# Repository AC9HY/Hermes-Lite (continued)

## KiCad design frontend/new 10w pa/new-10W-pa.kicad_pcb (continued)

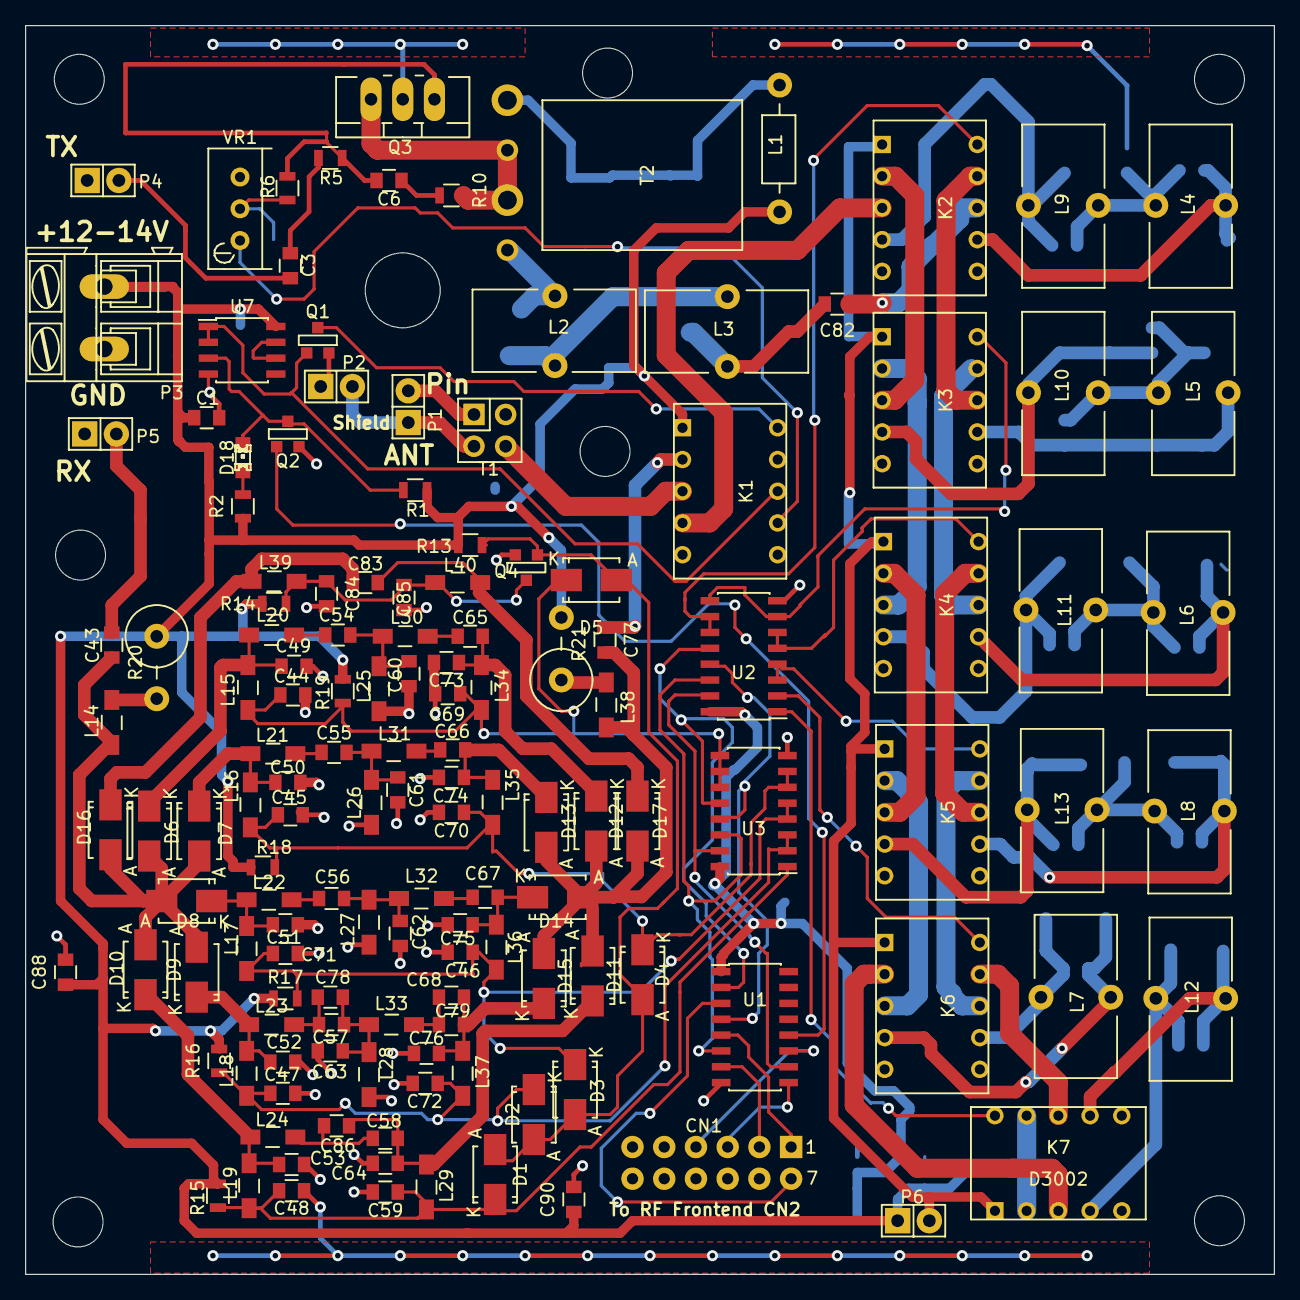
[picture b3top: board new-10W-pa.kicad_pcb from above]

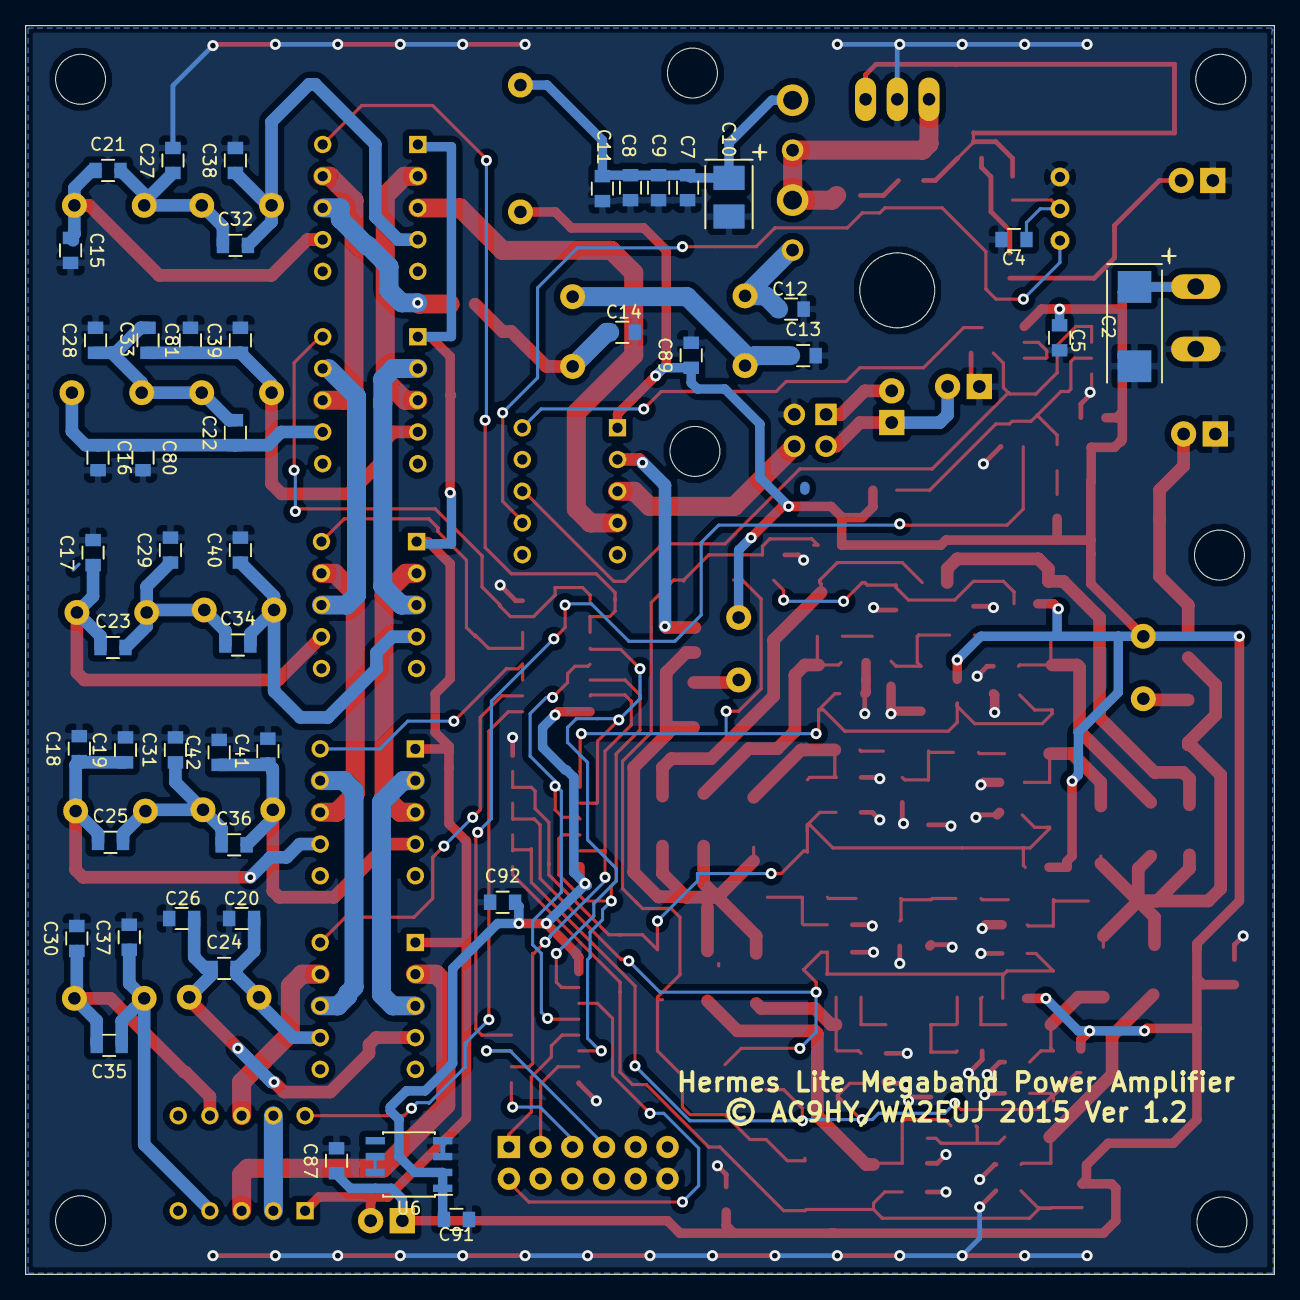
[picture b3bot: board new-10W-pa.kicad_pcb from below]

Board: 2 copper layers, 100.0 x 100.0 mm, 198 parts (46 on the bottom side), 107 nets.

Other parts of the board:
MountingHole_4mm, MountingHole_4mm#2, MountingHole_4mm#3, MountingHole_4mm#4, MountingHole_4mm#5, MountingHole_4mm#6, MountingHole_4mm#7: VAL**; MountingHole_4mm
MountingHole_6mm: VAL**; MountingHole_6mm

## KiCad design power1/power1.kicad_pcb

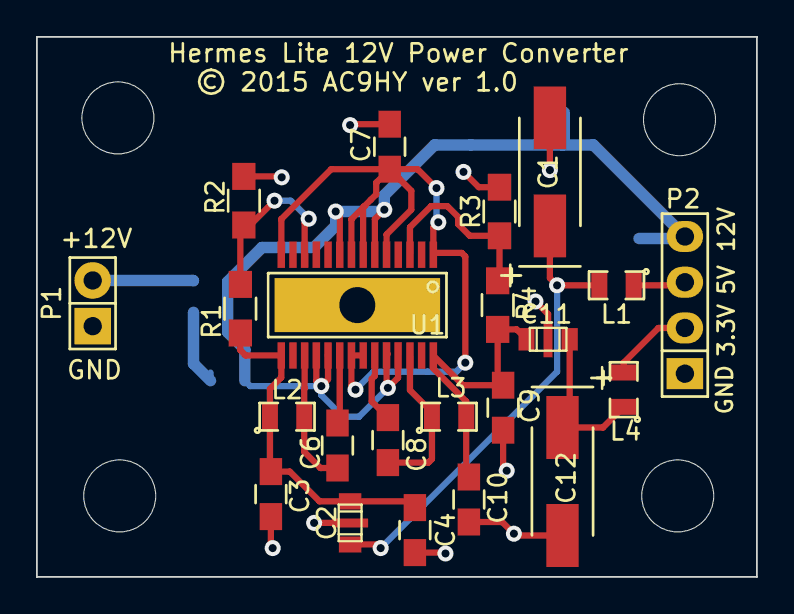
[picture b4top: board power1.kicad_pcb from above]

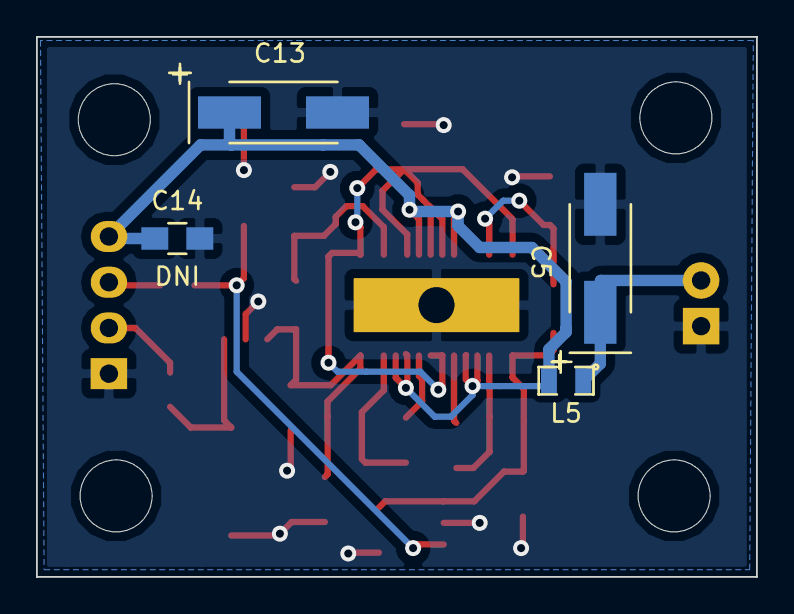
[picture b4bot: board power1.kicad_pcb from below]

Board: 2 copper layers, 40.0 x 30.0 mm, 31 parts (4 on the bottom side), 16 nets.

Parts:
C1, C5, C12: 10uF 25V; TantalC_SizeC_EIA-6032_HandSoldering
C2, C11: NFM21PC224R1C3D; cfeed_0805
C3, C6, C8, C10: 0.1uF; C_0805_HandSoldering
C4, C7, C9: 22uF; C_0805_HandSoldering
C13: DNI; TantalC_SizeC_EIA-6032_HandSoldering
C14: DNI; C_0805_HandSoldering
L1, L4: BLM21PG121SN1D; SMD-0805
L2: 1.5 uH; SMD-0805
L3: 1 uH; SMD-0805
L5: BLM21PG220SN1D; SMD-0805
MountingHole_4mm, MountingHole_4mm#2, MountingHole_4mm#3, MountingHole_4mm#4: VAL**; MountingHole_4mm
P1: CONN_01X02; Pin_Header_Straight_1x02
P2: CONN_01X04; Pin_Header_Straight_1x04
R1: 73.2k; R_0805_HandSoldering
R2, R3: 10k; R_0805_HandSoldering
R4: 45.3k; R_0805_HandSoldering
TH-OVAL: VAL**; TH-OVAL
U1: LT3633; TSSOP-28

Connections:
GND: C1.2, C2.3, C3.2, C4.2, C5.2, C7.2, C9.2, C10.2, C11.3, C12.2, C13.2, C14.2, P1.1, P2.1, R2.1, R3.1, TH-OVAL.1
unnamed: C1.1, C2.1, L1.2
unnamed: C2.2, C3.1, C4.1, L2.1, R1.2, U1.15
unnamed: C5.1, L5.1, P1.2
unnamed: C6.1, U1.20
unnamed: C6.2, L2.2, U1.17
unnamed: C7.1, U1.1, U1.5, U1.7, U1.8, U1.14, U1.21, U1.22
unnamed: C8.1, L3.1, U1.26
unnamed: C8.2, U1.23
unnamed: C9.1, C10.1, C11.1, L3.2, R4.1, U1.28
unnamed: C11.2, C12.1, L4.1
unnamed: C13.1, C14.1, L5.2, P2.4, U1.6, U1.9, U1.18, U1.19, U1.24, U1.25
unnamed: L1.1, P2.3
unnamed: L4.2, P2.2
unnamed: R1.1, R2.2, U1.12
unnamed: R3.2, R4.2, U1.3

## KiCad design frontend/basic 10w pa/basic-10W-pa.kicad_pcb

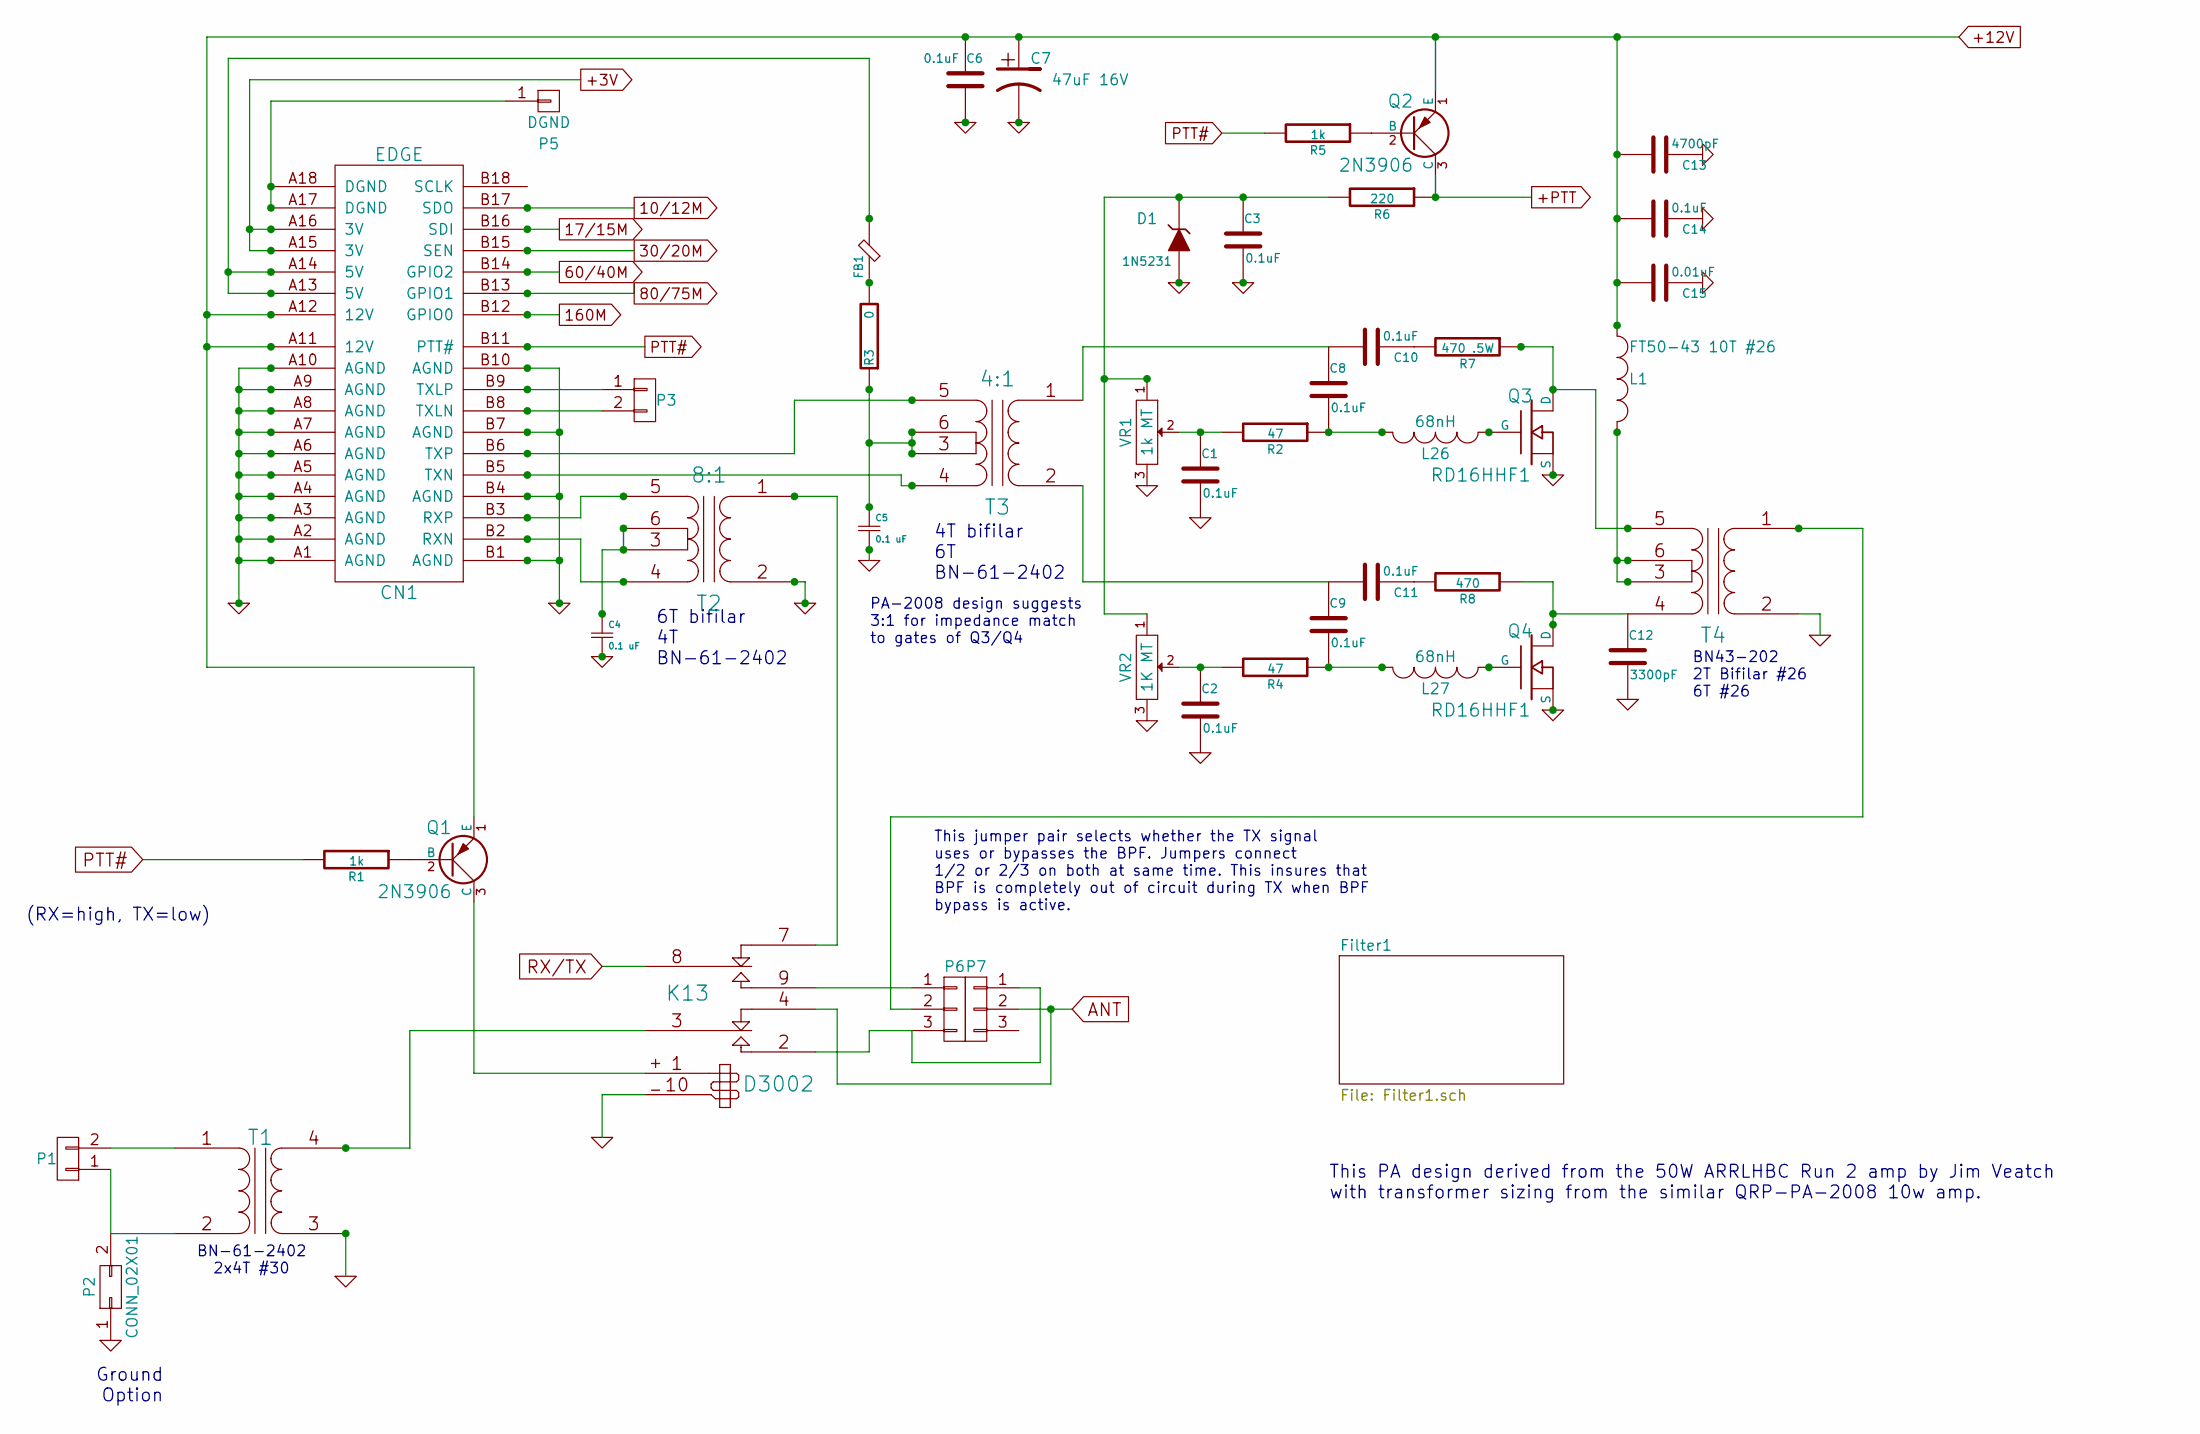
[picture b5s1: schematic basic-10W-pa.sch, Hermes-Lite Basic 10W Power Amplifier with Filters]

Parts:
C1, C2, C3, C6, C8, C9, C10, C11, C14: 0.1uF; C_0805_HandSoldering
C4, C5: 0.1 uF; C_0805_HandSoldering
C7: 47uF 16V; C1V8
C12: 3300pF; C_0805_HandSoldering
C13: 4700pF; C_0805_HandSoldering
C15: 0.01uF; C_0805_HandSoldering
CN1: EDGE
D1: 1N5231; Diode-SMA_Handsoldering
FB1: FB; SMD-0805
K13: D3002; DIP-10__300
L1: FT50-43 10T #26; Choke_Horizontal_RM10mm
L26, L27: 68nH; SMD-0805
P1: CONN_01X02; Pin_Header_Angled_1x02
P2: CONN_02X01; Pin_Header_Straight_1x02
P3: CONN_01X02; Pin_Header_Straight_1x02
P5: DGND; Pin_Header_Straight_1x01
P6, P7: CONN_01X03; Pin_Header_Straight_1x03
Q1, Q2: 2N3906; sot23
Q3, Q4: RD16HHF1; TO-220_Neutral123_Vertical_LargePads
R1, R5: 1k; R_0805_HandSoldering
R2, R4: 47; R_0805_HandSoldering
R3: 0; R_0805_HandSoldering
R6: 220; R_0805_HandSoldering
R7: 470 .5W; R_0805_HandSoldering
R8: 470; R_0805_HandSoldering
T1: TRANSFO; Socket_Strip_Straight_2x02
T2: 8:1; TRANSF
T3: 4:1; TRANSF
T4: TRANSF
VR1: 1k MT; Potentiometer_Bourns_3296W_3-8Zoll_Inline_ScrewUp
VR2: 1K MT; Potentiometer_Bourns_3296W_3-8Zoll_Inline_ScrewUp

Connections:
10/12M: CN1.B17 (SDO); also elsewhere on the board
17/15M: CN1.B16 (SDI); also elsewhere on the board
30/20M: CN1.B15 (SEN); also elsewhere on the board
60/40M: CN1.B14 (GPIO2); also elsewhere on the board
80/75M: CN1.B13 (GPIO1); also elsewhere on the board
160M: CN1.B12 (GPIO0); also elsewhere on the board
+3V: CN1.A15 (3V), CN1.A16 (3V)
+12V: C6.1, C7.1, C13.2, C14.2, C15.2, CN1.A11 (12V), CN1.A12 (12V), L1.1, Q1.1 (E), Q2.1 (E); also elsewhere on the board
+PTT: Q2.3 (C), R6.1; also elsewhere on the board
ANT: K13.4 (R1), P7.2; also elsewhere on the board
GND: C1.2, C2.2, C3.2, C4.2, C5.2, C6.2, C7.2, C12.2, C13.1, C14.1, C15.1, CN1.A1 (AGND), CN1.A2 (AGND), CN1.A3 (AGND), CN1.A4 (AGND), CN1.A5 (AGND), CN1.A6 (AGND), CN1.A7 (AGND), CN1.A8 (AGND), CN1.A9 (AGND), CN1.A10 (AGND), CN1.B1 (AGND), CN1.B4 (AGND), CN1.B7 (AGND), CN1.B10 (AGND), D1.1 (A), K13.10 (-), P2.1, Q3.2 (S), Q4.2 (S), T1.3 (SA), T2.2 (S2), T4.2 (S2), VR1.3, VR2.3; also elsewhere on the board
unnamed: C1.1, R2.2, VR1.2
unnamed: C2.1, R4.2, VR2.2
unnamed: C3.1, D1.2 (K), R6.2, VR1.1, VR2.1
unnamed: C4.1, T2.3 (PM), T2.6 (PM)
unnamed: C5.1, R3.1, T3.3 (PM), T3.6 (PM)
unnamed: C8.2, L26.2, R2.1
unnamed: C9.2, L27.2, R4.1
unnamed: C10.1, R7.2
unnamed: C8.1, C10.2, T3.1 (S1)
unnamed: C11.1, R8.2
unnamed: C9.1, C11.2, T3.2 (S2)
unnamed: C12.1, Q4.3 (D), R8.1, T4.4
unnamed: CN1.A13 (5V), CN1.A14 (5V), FB1.1
unnamed: CN1.A17 (DGND), CN1.A18 (DGND), P5.1
unnamed: CN1.B2 (RXN), T2.4
unnamed: CN1.B3 (RXP), T2.5
unnamed: CN1.B5 (TXN), T3.4
unnamed: CN1.B6 (TXP), T3.5
unnamed: CN1.B8 (TXLN), P3.2
unnamed: CN1.B9 (TXLP), P3.1
unnamed: FB1.2, R3.2
unnamed: K13.1 (+), Q1.3 (C)
unnamed: K13.2 (T1), P6.3, P7.1
unnamed: K13.3 (C1), T1.4 (SB)
unnamed: K13.7 (R2), T2.1 (S1)
unnamed: K13.9 (T2), P6.1
unnamed: L1.2, T4.3 (PM), T4.6 (PM)
unnamed: L26.1, Q3.1 (G)
unnamed: L27.1, Q4.1 (G)
unnamed: P1.1, P2.2, T1.2 (AB)
unnamed: P1.2, T1.1 (AA)
unnamed: P6.2, T4.1 (S1)
unnamed: Q1.2 (B), R1.1
unnamed: Q2.2 (B), R5.1
unnamed: Q3.3 (D), R7.1, T4.5
PTT#: CN1.B11 (PTT#), R1.2, R5.2
RX/TX: K13.8 (C2); also elsewhere on the board

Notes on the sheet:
6T bifilar 4T BN-61-2402
4T bifilar 6T BN-61-2402
Ground Option
BN-61-2402 2x4T #30
(RX=high, TX=low)
This jumper pair selects whether the TX signal uses or bypasses the BPF. Jumpers connect 1/2 or 2/3 on both at same time. This insures that BPF is completely out of circuit during TX when BPF bypass is active.
BN43-202 2T Bifilar #26 6T #26
PA-2008 design suggests 3:1 for impedance match to gates of Q3/Q4
This PA design derived from the 50W ARRLHBC Run 2 amp by Jim Veatch with transformer sizing from the similar QRP-PA-2008 10w amp.

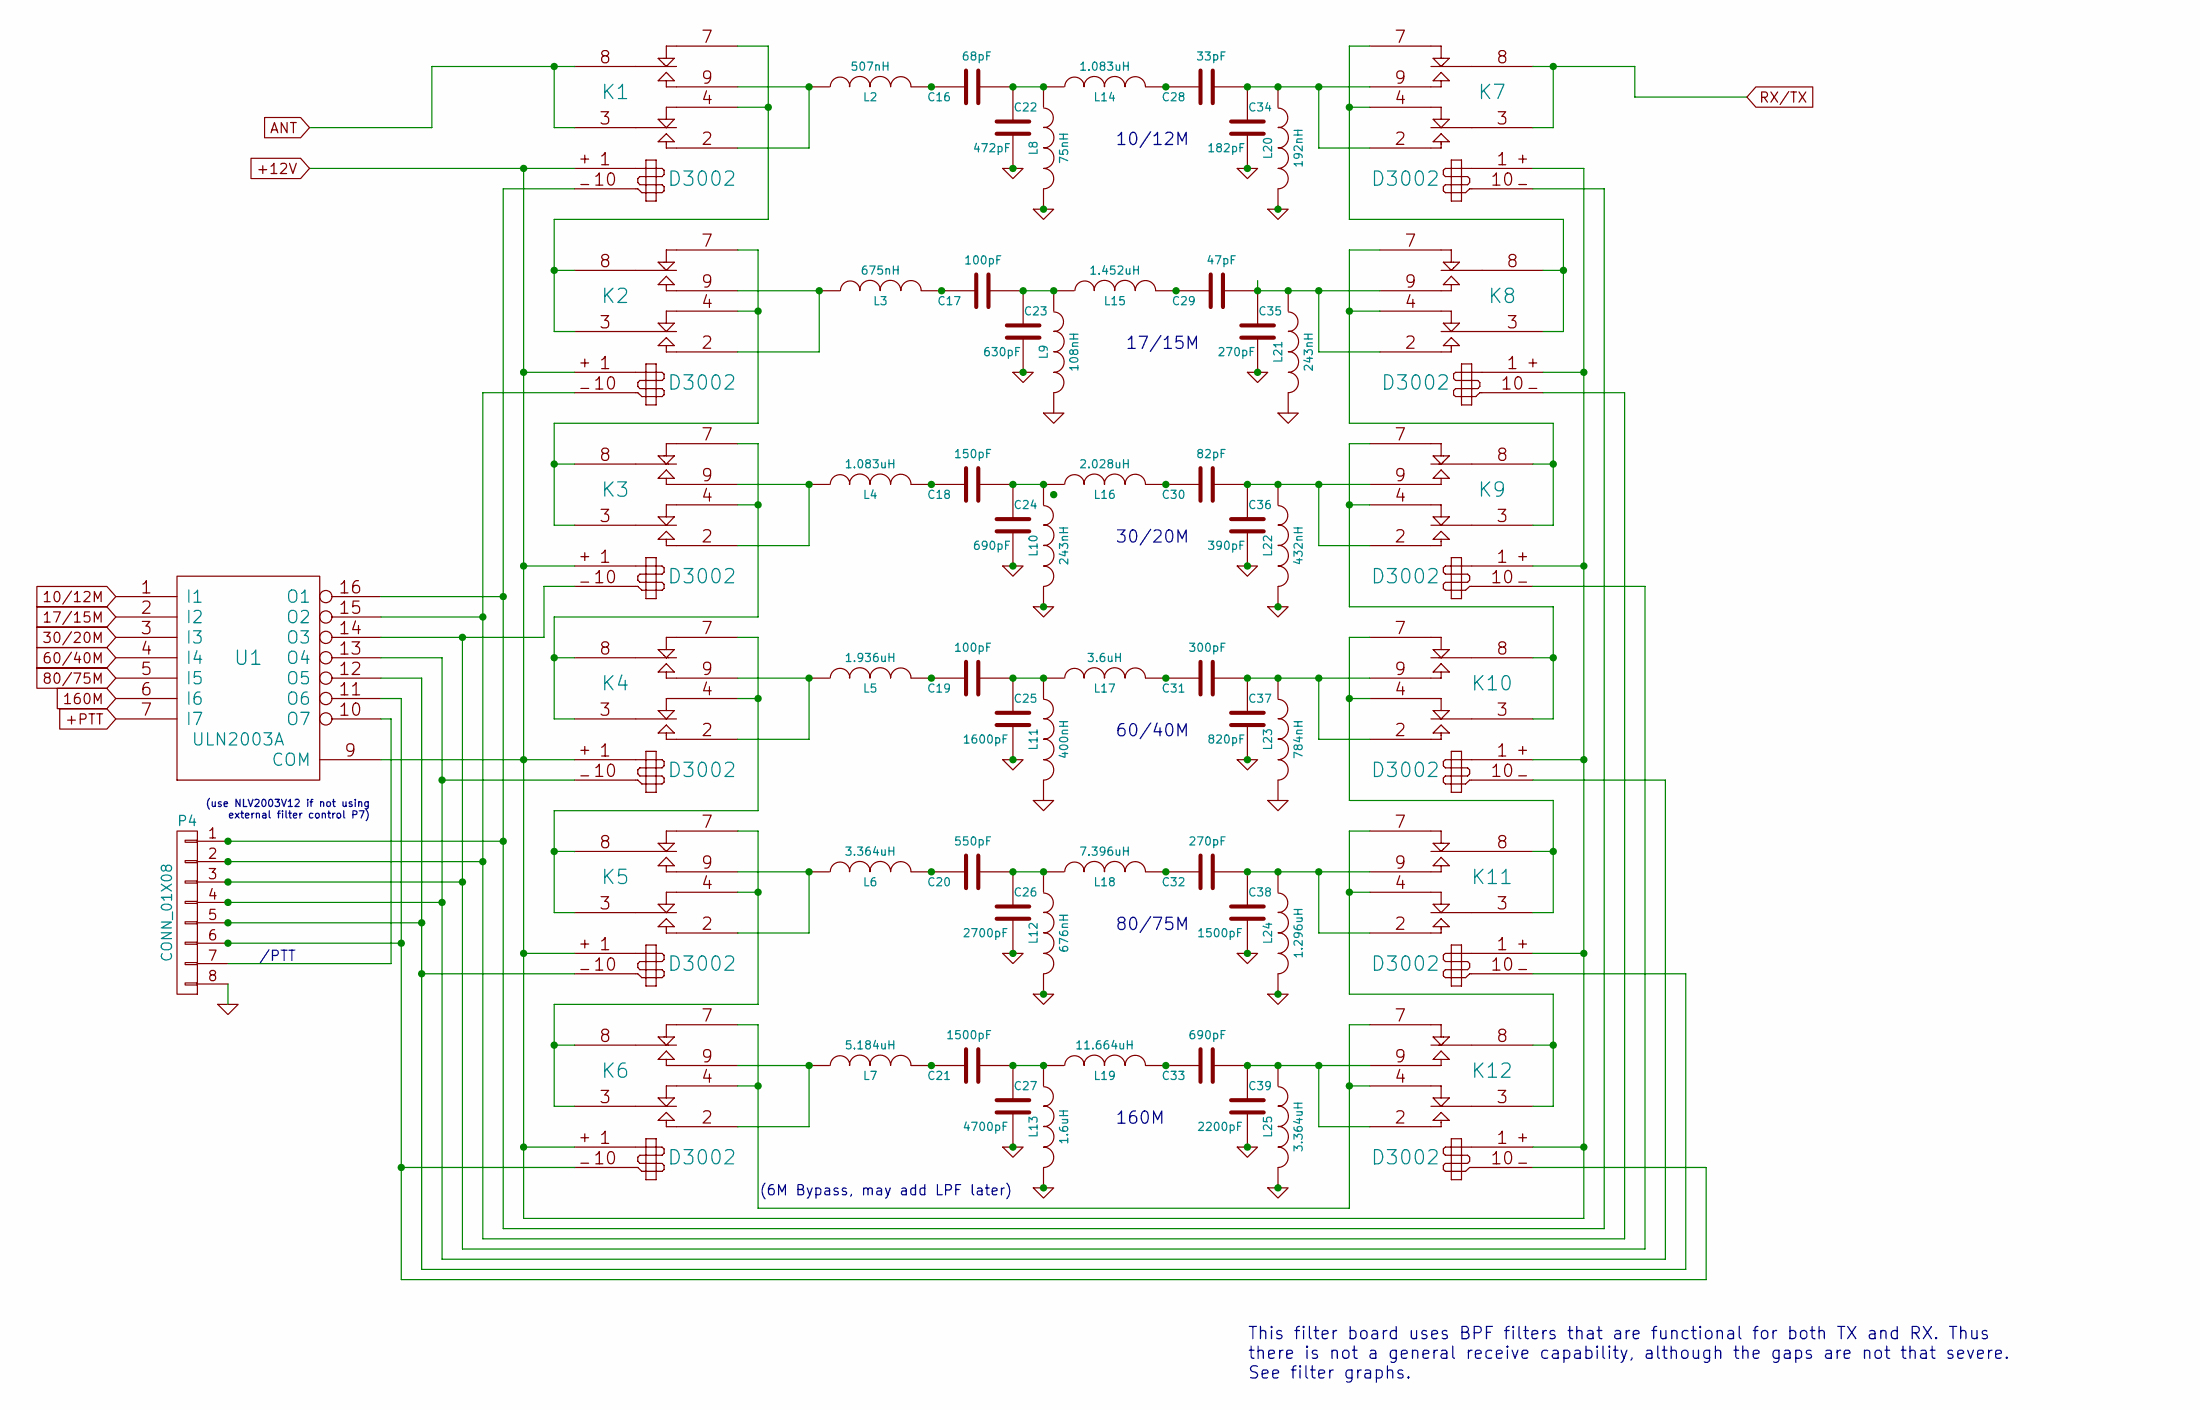
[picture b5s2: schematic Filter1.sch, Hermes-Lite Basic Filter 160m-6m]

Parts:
C16: 68pF; C_0805_HandSoldering
C17, C19: 100pF; C_0805_HandSoldering
C18: 150pF; C_0805_HandSoldering
C20: 550pF; C_0805_HandSoldering
C21, C38: 1500pF; C_0805_HandSoldering
C22: 472pF; C_0805_HandSoldering
C23: 630pF; C_0805_HandSoldering
C24, C33: 690pF; C_0805_HandSoldering
C25: 1600pF; C_0805_HandSoldering
C26: 2700pF; C_0805_HandSoldering
C27: 4700pF; C_0805_HandSoldering
C28: 33pF; C_0805_HandSoldering
C29: 47pF; C_0805_HandSoldering
C30: 82pF; C_0805_HandSoldering
C31: 300pF; C_0805_HandSoldering
C32, C35: 270pF; C_0805_HandSoldering
C34: 182pF; C_0805_HandSoldering
C36: 390pF; C_0805_HandSoldering
C37: 820pF; C_0805_HandSoldering
C39: 2200pF; C_0805_HandSoldering
K1, K2, K3, K4, K5, K6, K7, K8, K9, K10, K11, K12: D3002; DIP-10__300
L2: 507nH; Choke_Toroid_6,5x13mm_Vertical
L3: 675nH; Choke_Toroid_6,5x13mm_Vertical
L4, L14: 1.083uH; Choke_Toroid_6,5x13mm_Vertical
L5: 1.936uH; Choke_Toroid_6,5x13mm_Vertical
L6, L25: 3.364uH; Choke_Toroid_6,5x13mm_Vertical
L7: 5.184uH; Choke_Toroid_6,5x13mm_Vertical
L8: 75nH; Choke_Toroid_6,5x13mm_Vertical
L9: 108nH; Choke_Toroid_6,5x13mm_Vertical
L10, L21: 243nH; Choke_Toroid_6,5x13mm_Vertical
L11: 400nH; Choke_Toroid_6,5x13mm_Vertical
L12: 676nH; Choke_Toroid_6,5x13mm_Vertical
L13: 1.6uH; Choke_Toroid_6,5x13mm_Vertical
L15: 1.452uH; Choke_Toroid_6,5x13mm_Vertical
L16: 2.028uH; Choke_Toroid_6,5x13mm_Vertical
L17: 3.6uH; Choke_Toroid_6,5x13mm_Vertical
L18: 7.396uH; Choke_Toroid_6,5x13mm_Vertical
L19: 11.664uH; Choke_Toroid_6,5x13mm_Vertical
L20: 192nH; Choke_Toroid_6,5x13mm_Vertical
L22: 432nH; Choke_Toroid_6,5x13mm_Vertical
L23: 784nH; Choke_Toroid_6,5x13mm_Vertical
L24: 1.296uH; Choke_Toroid_6,5x13mm_Vertical
P4: CONN_01X08; Pin_Header_Straight_1x08
U1: ULN2003A; DIP-16__300

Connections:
10/12M: U1.1 (I1); also elsewhere on the board
17/15M: U1.2 (I2); also elsewhere on the board
30/20M: U1.3 (I3); also elsewhere on the board
60/40M: U1.4 (I4); also elsewhere on the board
80/75M: U1.5 (I5); also elsewhere on the board
160M: U1.6 (I6); also elsewhere on the board
+12V: K1.1 (+), K2.1 (+), K3.1 (+), K4.1 (+), K5.1 (+), K6.1 (+), K7.1 (+), K8.1 (+), K9.1 (+), K10.1 (+), K11.1 (+), K12.1 (+), U1.9 (COM); also elsewhere on the board
+PTT: U1.7 (I7); also elsewhere on the board
ANT: K1.3 (C1), K1.8 (C2); also elsewhere on the board
GND: C22.2, C23.2, C24.2, C25.2, C26.2, C27.2, C34.2, C35.2, C36.2, C37.2, C38.2, C39.2, L8.2, L9.2, L10.2, L11.2, L12.2, L13.2, L20.2, L21.2, L22.2, L23.2, L24.2, L25.2, P4.8, U1.8 (GND); also elsewhere on the board
unnamed: C16.1, L2.2
unnamed: C16.2, C22.1, L8.1, L14.1
unnamed: C17.1, L3.2
unnamed: C17.2, C23.1, L9.1, L15.1
unnamed: C18.1, L4.2
unnamed: C18.2, C24.1, L10.1, L16.1
unnamed: C19.1, L5.2
unnamed: C19.2, C25.1, L11.1, L17.1
unnamed: C20.1, L6.2
unnamed: C20.2, C26.1, L12.1, L18.1
unnamed: C21.1, L7.2
unnamed: C21.2, C27.1, L13.1, L19.1
unnamed: C28.1, L14.2
unnamed: C28.2, C34.1, K7.2 (T1), K7.9 (T2), L20.1
unnamed: C29.1, L15.2
unnamed: C29.2, C35.1, K8.2 (T1), K8.9 (T2), L21.1
unnamed: C30.1, L16.2
unnamed: C30.2, C36.1, K9.2 (T1), K9.9 (T2), L22.1
unnamed: C31.1, L17.2
unnamed: C31.2, C37.1, K10.2 (T1), K10.9 (T2), L23.1
unnamed: C32.1, L18.2
unnamed: C32.2, C38.1, K11.2 (T1), K11.9 (T2), L24.1
unnamed: C33.1, L19.2
unnamed: C33.2, C39.1, K12.2 (T1), K12.9 (T2), L25.1
unnamed: K1.2 (T1), K1.9 (T2), L2.1
unnamed: K1.4 (R1), K1.7 (R2), K2.3 (C1), K2.8 (C2)
unnamed: K1.10 (-), K7.10 (-), P4.1, U1.16 (O1)
unnamed: K2.2 (T1), K2.9 (T2), L3.1
unnamed: K2.4 (R1), K2.7 (R2), K3.3 (C1), K3.8 (C2)
unnamed: K2.10 (-), K8.10 (-), P4.2, U1.15 (O2)
unnamed: K3.2 (T1), K3.9 (T2), L4.1
unnamed: K3.4 (R1), K3.7 (R2), K4.3 (C1), K4.8 (C2)
unnamed: K3.10 (-), K9.10 (-), P4.3, U1.14 (O3)
unnamed: K4.2 (T1), K4.9 (T2), L5.1
unnamed: K4.4 (R1), K4.7 (R2), K5.3 (C1), K5.8 (C2)
unnamed: K5.2 (T1), K5.9 (T2), L6.1
unnamed: K5.4 (R1), K5.7 (R2), K6.3 (C1), K6.8 (C2)
unnamed: K6.2 (T1), K6.9 (T2), L7.1
unnamed: K7.4 (R1), K7.7 (R2), K8.3 (C1), K8.8 (C2)
unnamed: K8.4 (R1), K8.7 (R2), K9.3 (C1), K9.8 (C2)
unnamed: K9.4 (R1), K9.7 (R2), K10.3 (C1), K10.8 (C2)
unnamed: K10.4 (R1), K10.7 (R2), K11.3 (C1), K11.8 (C2)
unnamed: K4.10 (-), K10.10 (-), P4.4, U1.13 (O4)
unnamed: K11.4 (R1), K11.7 (R2), K12.3 (C1), K12.8 (C2)
unnamed: K5.10 (-), K11.10 (-), P4.5, U1.12 (O5)
unnamed: K6.4 (R1), K6.7 (R2), K12.4 (R1), K12.7 (R2)
unnamed: K6.10 (-), K12.10 (-), P4.6, U1.11 (O6)
unnamed: P4.7, U1.10 (O7)
RX/TX: K7.3 (C1), K7.8 (C2); also elsewhere on the board

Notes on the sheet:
160M
80/75M
60/40M
30/20M
17/15M
10/12M
This filter board uses BPF filters that are functional for both TX and RX. Thus there is not a general receive capability, although the gaps are not that severe. See filter graphs.
(6M Bypass, may add LPF later)
(use NLV2003V12 if not using external filter control P7)
/PTT

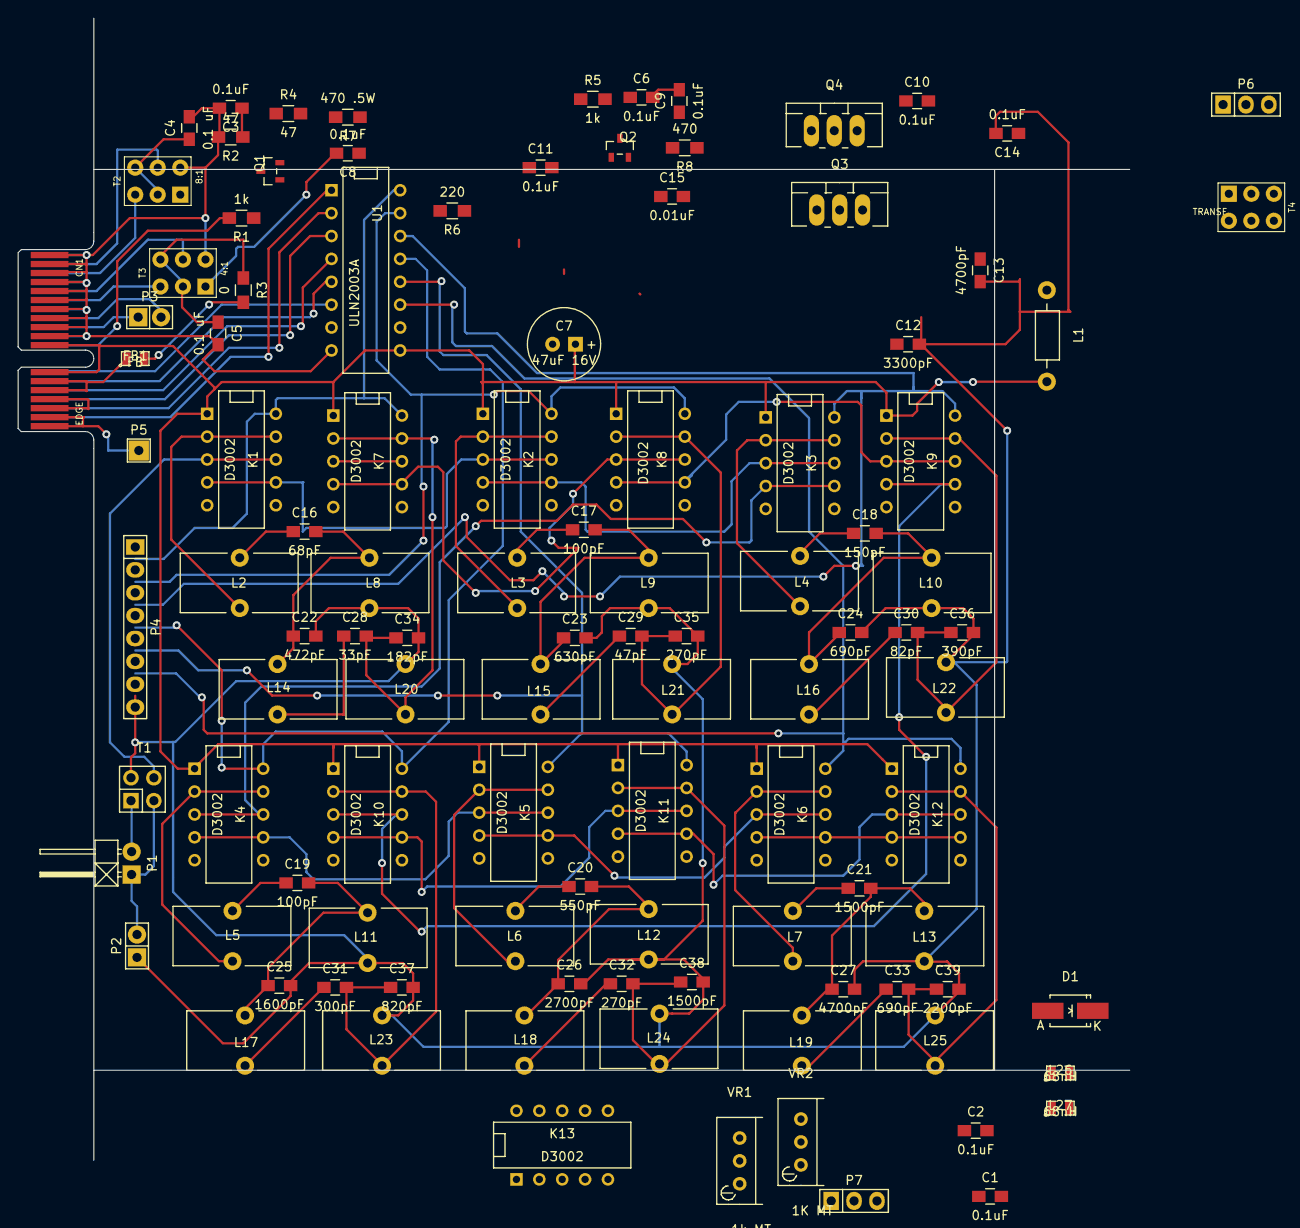
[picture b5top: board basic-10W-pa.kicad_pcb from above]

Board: 2 copper layers, 123.4 x 126.8 mm, 108 parts (0 on the bottom side), 96 nets.

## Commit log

2014-12-08 1W pa initial commit
2014-12-08 Preamp-Atten commit to save, not complete
2014-12-08 Alternate Alex Docs
2014-12-09 Minor updates on footprints
2014-12-16 Version 1.7 updates
2014-12-16 1.7 additional commit
2014-12-22 10W amp initial commit
2014-12-23 Cleanup BOM
2014-12-23 More BOM Cleanup
2014-12-23 Minor updates to costs
2014-12-26 Beginning updates for RD16HHF1 design
2015-01-01 Push new 10W design
2015-01-01 Board placement
2015-01-02 Minor updates to v1.12
2015-01-02 forgot to update pdf
2015-01-03 Starting Layout
2015-01-05 Continuing board routing
2015-01-06 Minor filter updates
2015-01-06 Continuing routing
2015-01-07 Plotting complete
2015-01-07 Minor silkscreen update
2015-01-10 new superband design and updated pcb
2015-01-11 Board files updated
2015-01-13 Upload latest pcb changes
2015-01-14 BOM updates
2015-01-14 Correct compnent naming and fix relay error
2015-01-15 Minor silkscreen bug
2015-01-15 Final PCB, hopefully
2015-01-17 New Power Converter Design
2015-01-17 heatsink change
2015-01-19 More pcb changes
2015-01-19 Board edge added
2015-01-20 Few more pcb changes
2015-01-20 Add SGND to circuit
2015-01-21 BCD Filter update
2015-01-22 Changes for new J16 approach
2015-01-26 Final pcd changes
2015-01-28 BOM and PCB updates
2015-02-03 PTT change
2015-02-12 Added opto and change of PTT
2015-02-23 Second pass of superband
2015-03-13 modify mounting holes
2015-03-26 final 1.2 changes
2015-03-26 update pdf
2015-03-30 first pass for Oshpark
2015-04-12 cleanup, minor superband changes
